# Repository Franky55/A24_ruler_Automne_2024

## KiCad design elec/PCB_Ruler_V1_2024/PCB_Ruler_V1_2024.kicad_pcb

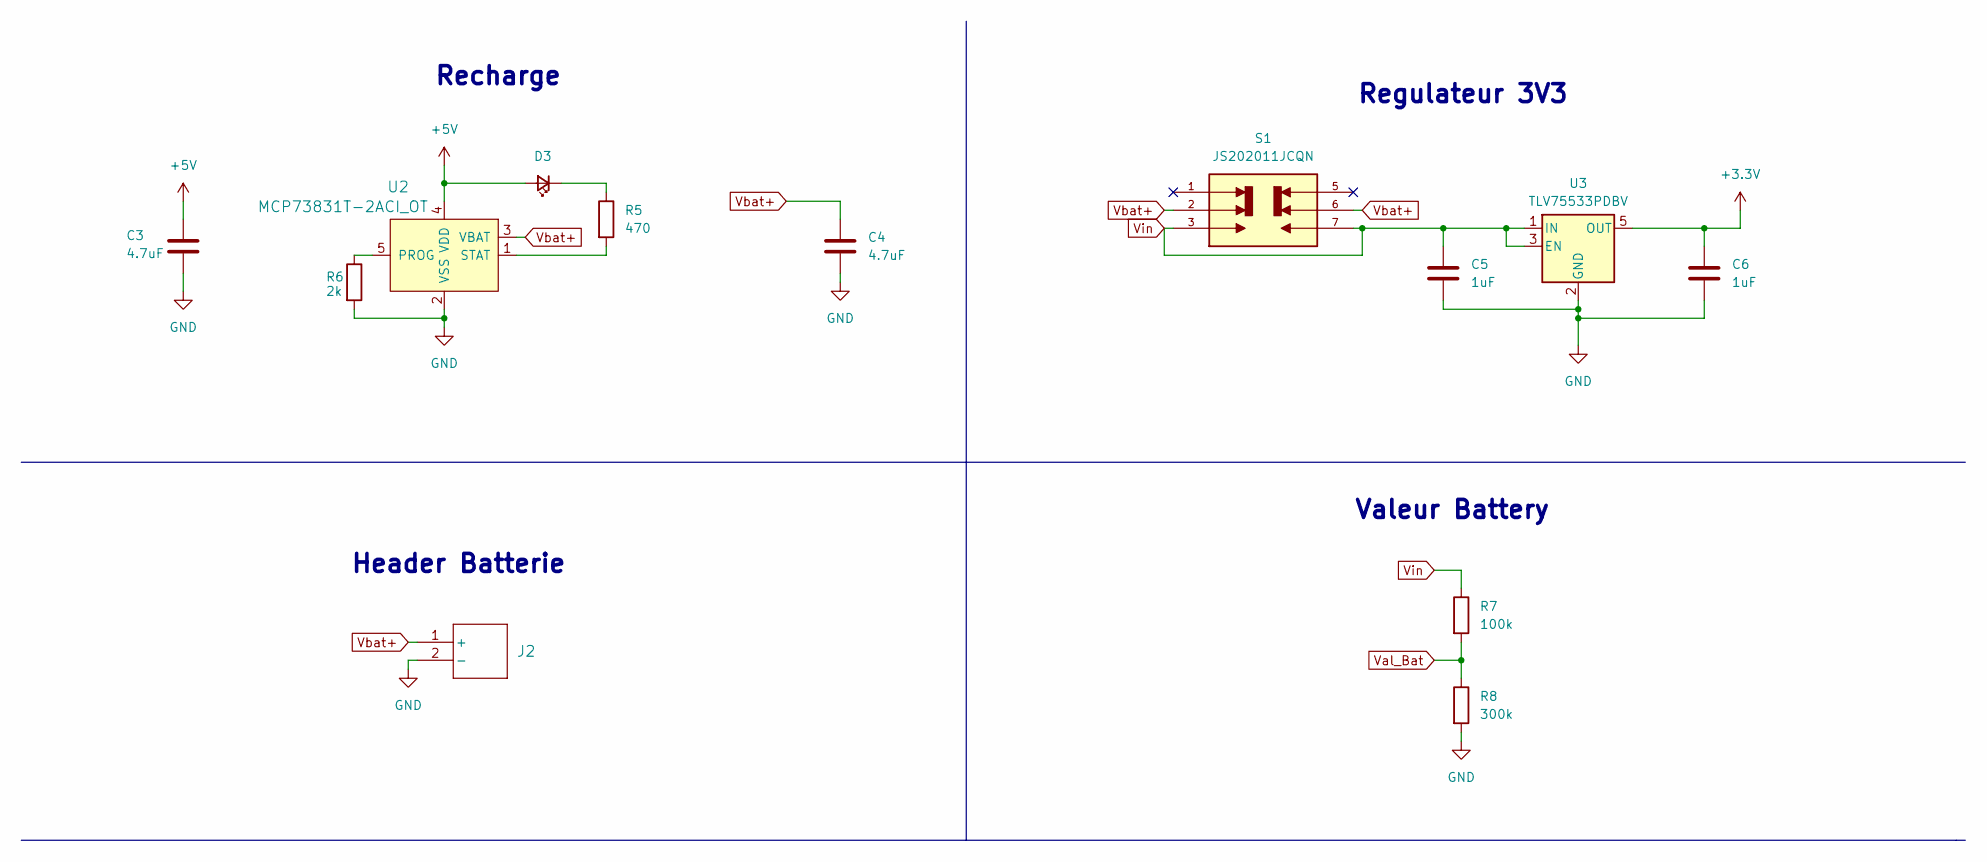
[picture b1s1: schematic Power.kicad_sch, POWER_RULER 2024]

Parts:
C3, C4: 4.7uF; C_0603_1608Metric_Pad1.08x0.95mm_HandSolder
C5, C6: 1uF; C_0603_1608Metric_Pad1.08x0.95mm_HandSolder
D3: LED_Small; LED_0603_1608Metric_Pad1.05x0.95mm_HandSolder
J2: S2B-XH-A-1LFSN; JST_XH_S2B-XH-A-1_1x02_P2.50mm_Horizontal
R5: 470; R_0603_1608Metric_Pad0.98x0.95mm_HandSolder
R6: 2k; R_0603_1608Metric_Pad0.98x0.95mm_HandSolder
R7: 100k; R_0603_1608Metric_Pad0.98x0.95mm_HandSolder
R8: 300k; R_0603_1608Metric_Pad0.98x0.95mm_HandSolder
S1: JS202011JCQN; SW_JS202011JCQN; PARTREV 11 Nov 19
U2: MCP73831T-2ACI_OT; SOT-753; MPN MCP73831T-2ACI/OT; Digi-Key_PN MCP73831T-2ACI/OTCT-ND
U3: TLV75533PDBV; SOT-23-5

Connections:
+5V: C3.1, D3.2 (A), U2.4 (VDD); also elsewhere on the board
AVDD: C6.1, U3.5 (OUT); also elsewhere on the board
GND: C3.2, C4.2, C5.2, C6.2, J2.2 (-), R6.2, R8.2, U2.2 (VSS), U3.2 (GND); also elsewhere on the board
unnamed: D3.1 (K), R5.1
unnamed: R6.1, U2.5 (PROG)
unnamed: R5.2, U2.1 (STAT)
Val_Bat: R7.2, R8.1; also elsewhere on the board
Vbat+: C4.1, J2.1 (+), S1.2, S1.6, U2.3 (VBAT)
Vin: C5.1, R7.1, S1.3, S1.7, U3.1 (IN), U3.3 (EN)

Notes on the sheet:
Valeur Battery
Header Batterie
Regulateur 3V3
Recharge

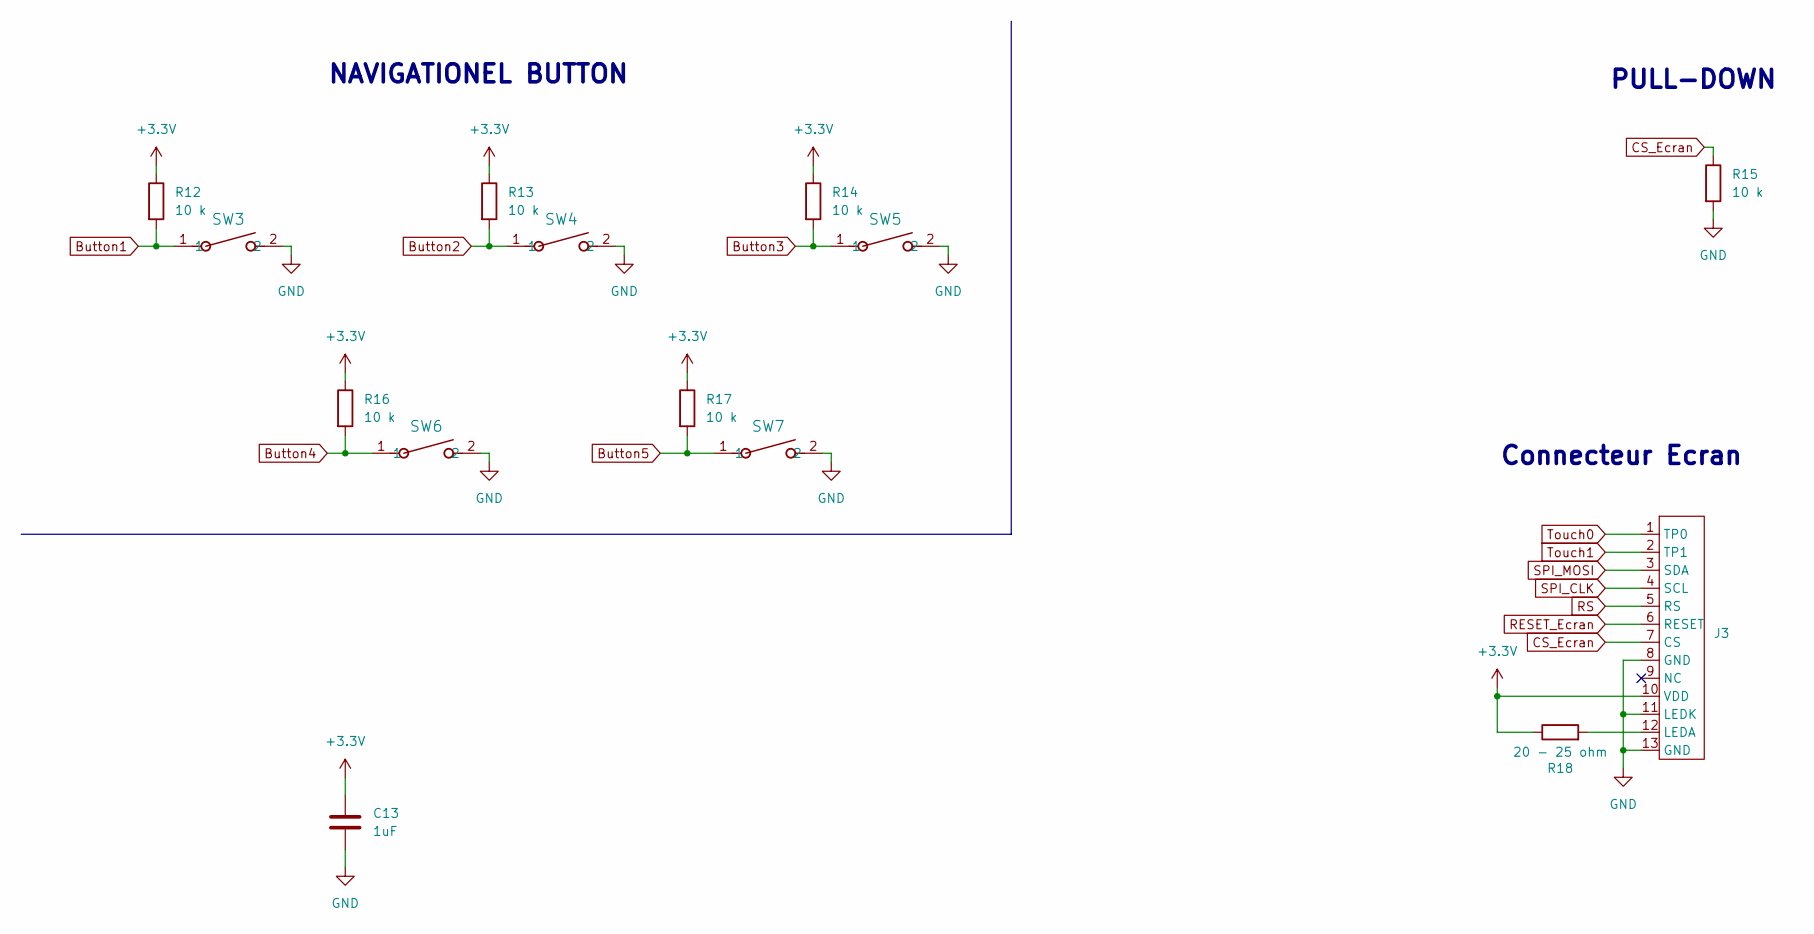
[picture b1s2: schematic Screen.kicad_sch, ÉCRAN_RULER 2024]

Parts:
C13: 1uF; C_0603_1608Metric_Pad1.08x0.95mm_HandSolder
J3: Hirose_FH12-13S-0.5SH_1x13-1MP_P0.50mm_Horizontal
R12, R13, R14, R15, R16, R17: 10 k; R_0603_1608Metric_Pad0.98x0.95mm_HandSolder
R18: 20 - 25 ohm; R_0603_1608Metric_Pad0.98x0.95mm_HandSolder
SW3, SW4, SW5, SW6, SW7: CS1213AGF260; SW_CS1213AGF260_CRS

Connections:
AVDD: C13.1, J3.10 (VDD), R12.1, R13.1, R14.1, R16.1, R17.1, R18.1; also elsewhere on the board
Button1: R12.2, SW3.1; also elsewhere on the board
Button2: R13.2, SW4.1; also elsewhere on the board
Button3: R14.2, SW5.1; also elsewhere on the board
Button4: R16.2, SW6.1; also elsewhere on the board
Button5: R17.2, SW7.1; also elsewhere on the board
CS_Ecran: J3.7 (CS), R15.1; also elsewhere on the board
GND: C13.2, J3.8 (GND), J3.11 (LEDK), J3.13 (GND), R15.2, SW3.2, SW4.2, SW5.2, SW6.2, SW7.2; also elsewhere on the board
unnamed: J3.12 (LEDA), R18.2
RESET_Ecran: J3.6 (RESET); also elsewhere on the board
RS: J3.5 (RS); also elsewhere on the board
SPI_CLK: J3.4 (SCL); also elsewhere on the board
SPI_MOSI: J3.3 (SDA); also elsewhere on the board
Touch0: J3.1 (TP0); also elsewhere on the board
Touch1: J3.2 (TP1); also elsewhere on the board

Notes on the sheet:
NAVIGATIONEL BUTTON
PULL-DOWN
Connecteur Ecran

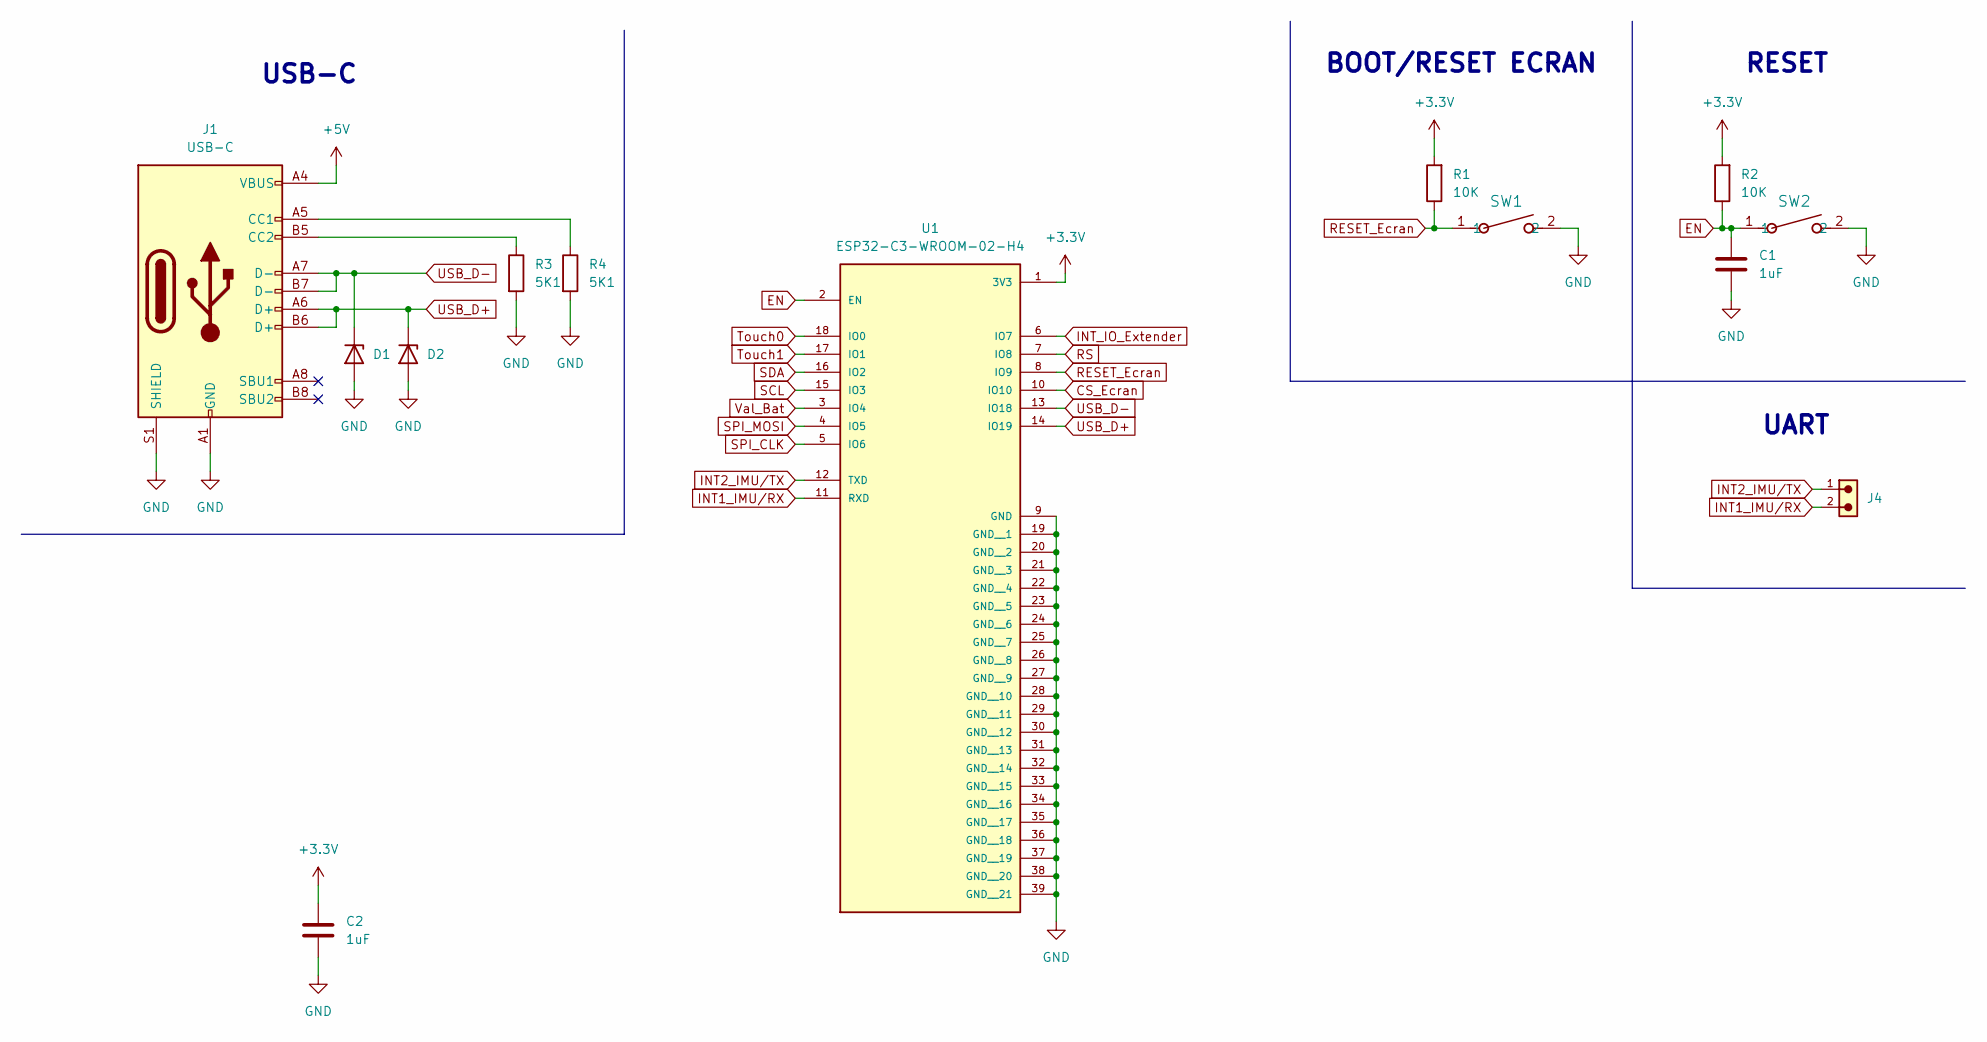
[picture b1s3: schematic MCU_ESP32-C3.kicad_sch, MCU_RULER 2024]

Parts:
C1, C2: 1uF; C_0603_1608Metric_Pad1.08x0.95mm_HandSolder
D1, D2: D_Zener; D_SOD-923
J1: USB-C; USB_C_Receptacle_G-Switch_GT-USB-7010ASV
J4: 61300211121; PART-NUMBER 61300211121
R1, R2: 10K; R_0603_1608Metric_Pad0.98x0.95mm_HandSolder
R3, R4: 5K1; R_0603_1608Metric_Pad0.98x0.95mm_HandSolder
SW1, SW2: CS1213AGF260; SW_CS1213AGF260_CRS
U1: ESP32-C3-WROOM-02-H4; MODULE_ESP32-C3-WROOM-02-H4

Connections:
+5V: J1.A4 (VBUS), J1.A9 (VBUS), J1.B4 (VBUS), J1.B9 (VBUS); also elsewhere on the board
AVDD: C2.1, R1.2, R2.2, U1.1 (3V3); also elsewhere on the board
CS_Ecran: U1.10 (IO10); also elsewhere on the board
EN: C1.1, R2.1, SW2.1, U1.2 (EN)
GND: C1.2, C2.2, D1.2 (A), D2.2 (A), J1.A1 (GND), J1.A12 (GND), J1.B1 (GND), J1.B12 (GND), J1.S1 (SHIELD), R3.2, R4.2, SW1.2, SW2.2, U1.9 (GND), U1.19 (GND__1), U1.20 (GND__2), U1.21 (GND__3), U1.22 (GND__4), U1.23 (GND__5), U1.24 (GND__6), U1.25 (GND__7), U1.26 (GND__8), U1.27 (GND__9), U1.28 (GND__10), U1.29 (GND__11), U1.30 (GND__12), U1.31 (GND__13), U1.32 (GND__14), U1.33 (GND__15), U1.34 (GND__16), U1.35 (GND__17), U1.36 (GND__18), U1.37 (GND__19), U1.38 (GND__20), U1.39 (GND__21); also elsewhere on the board
INT1_IMU/RX: J4.2, U1.11 (RXD); also elsewhere on the board
INT2_IMU/TX: J4.1, U1.12 (TXD); also elsewhere on the board
INT_IO_Extender: U1.6 (IO7); also elsewhere on the board
unnamed: J1.A5 (CC1), R4.1
unnamed: J1.B5 (CC2), R3.1
RESET_Ecran: R1.1, SW1.1, U1.8 (IO9); also elsewhere on the board
RS: U1.7 (IO8); also elsewhere on the board
SCL: U1.15 (IO3); also elsewhere on the board
SDA: U1.16 (IO2); also elsewhere on the board
SPI_CLK: U1.5 (IO6); also elsewhere on the board
SPI_MOSI: U1.4 (IO5); also elsewhere on the board
Touch0: U1.18 (IO0); also elsewhere on the board
Touch1: U1.17 (IO1); also elsewhere on the board
USB_D+: D2.1 (K), J1.A6 (D+), J1.B6 (D+), U1.14 (IO19)
USB_D-: D1.1 (K), J1.A7 (D-), J1.B7 (D-), U1.13 (IO18)
Val_Bat: U1.3 (IO4); also elsewhere on the board

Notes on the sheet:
RESET
UART
USB-C
BOOT/RESET ECRAN

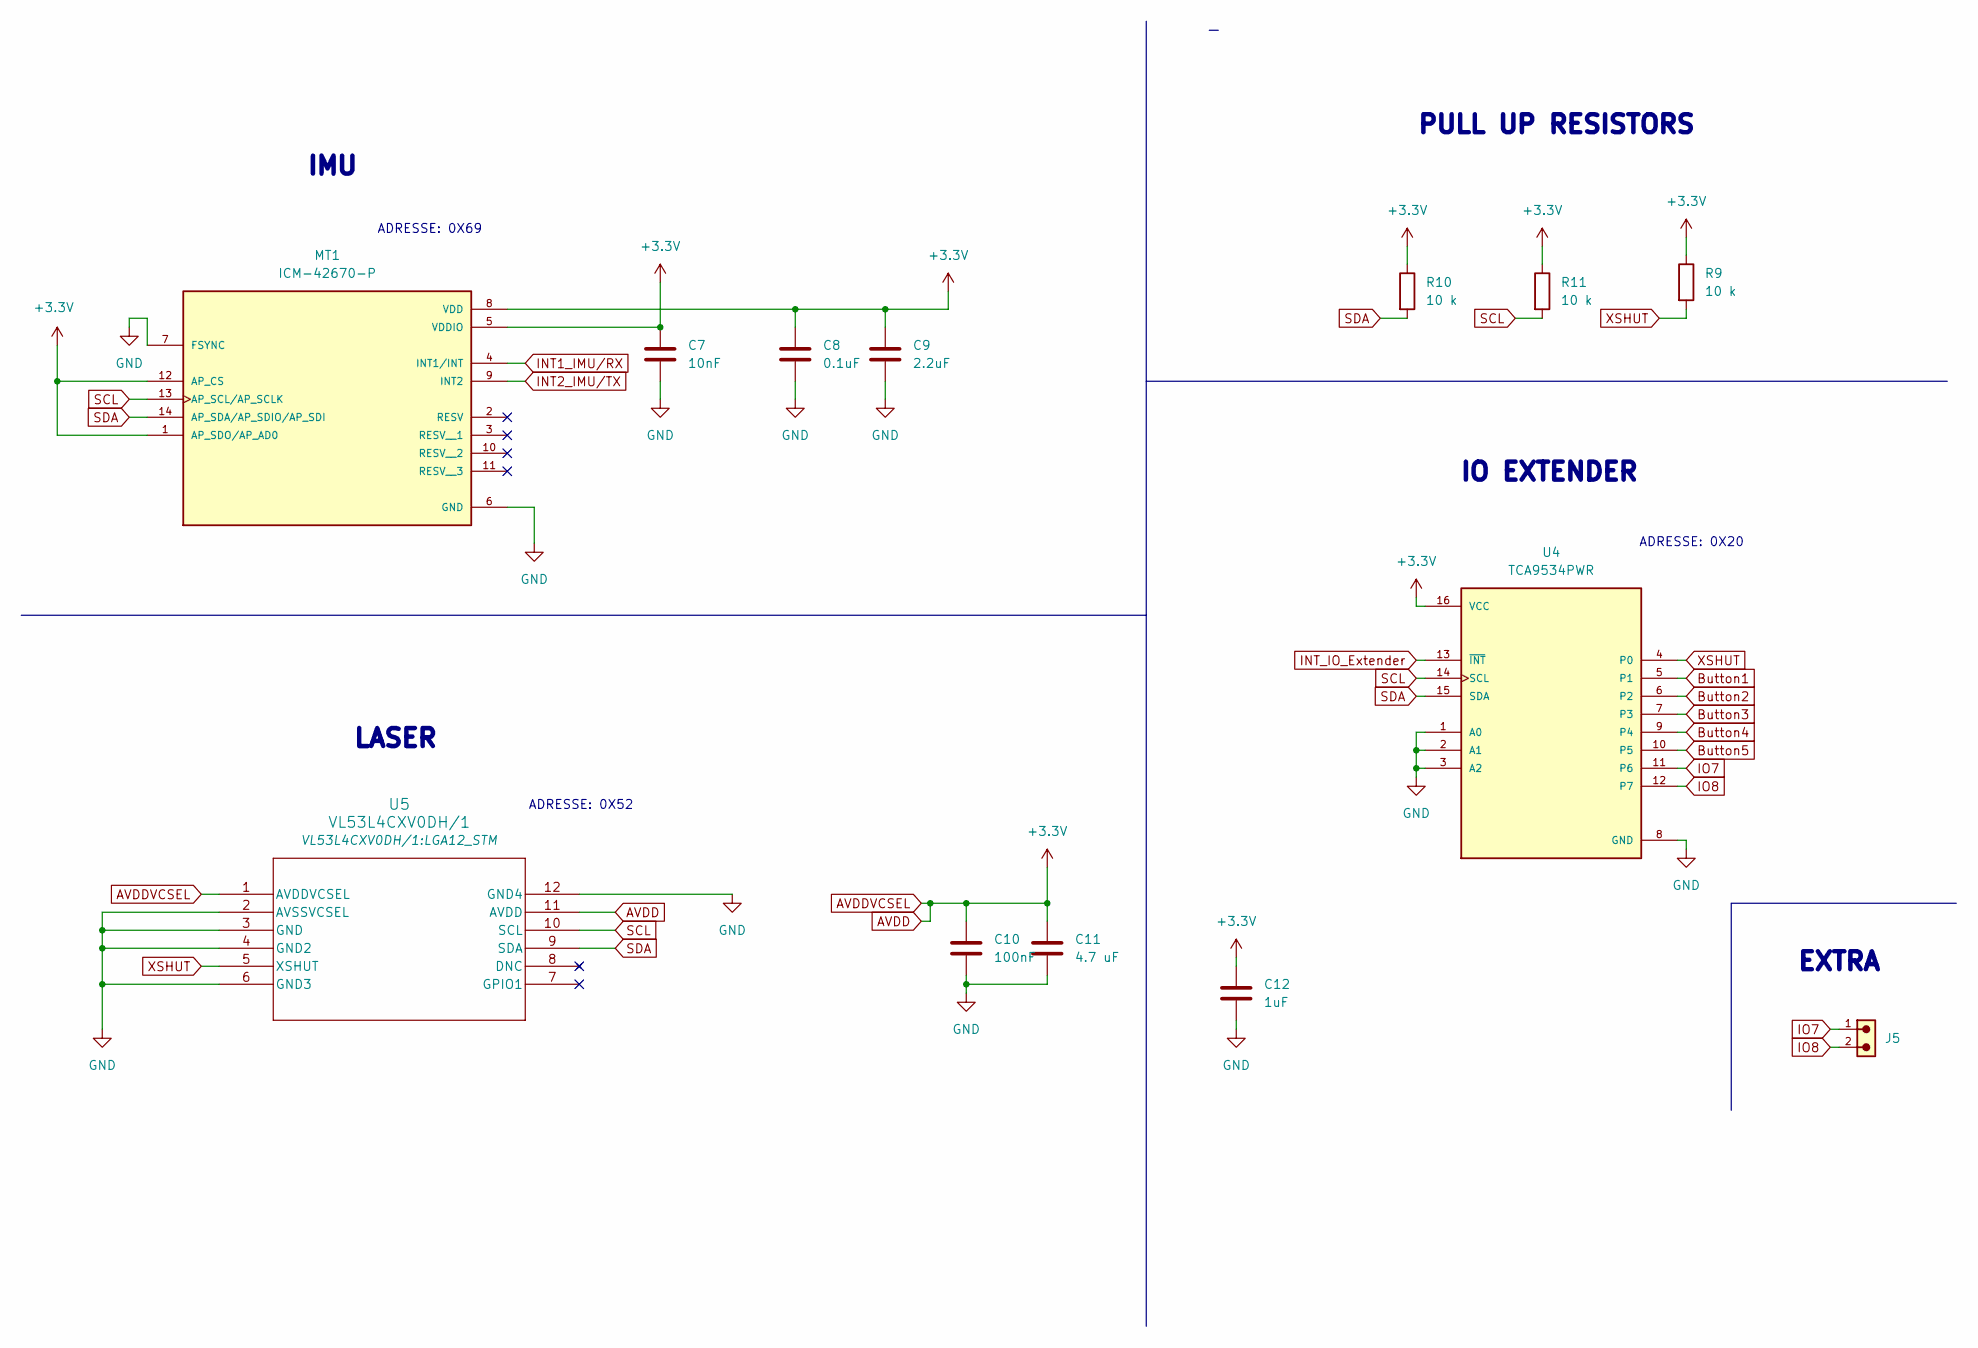
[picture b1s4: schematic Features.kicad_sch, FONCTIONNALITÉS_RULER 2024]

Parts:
C7: 10nF; C_0603_1608Metric_Pad1.08x0.95mm_HandSolder
C8: 0.1uF; C_0603_1608Metric_Pad1.08x0.95mm_HandSolder
C9: 2.2uF; C_0603_1608Metric_Pad1.08x0.95mm_HandSolder
C10: 100nF; C_0603_1608Metric_Pad1.08x0.95mm_HandSolder
C11: 4.7 uF; C_0603_1608Metric_Pad1.08x0.95mm_HandSolder
C12: 1uF; C_0603_1608Metric_Pad1.08x0.95mm_HandSolder
J5: 61300211121; PART-NUMBER 61300211121
MT1: ICM-42670-P; XDCR_ICM-42670-P; PARTREV 1.1
R9, R10, R11: 10 k; R_0603_1608Metric_Pad0.98x0.95mm_HandSolder
U4: TCA9534PWR; SOP65P640X120-16N; PARTREV D
U5: VL53L4CXV0DH/1; LGA12_STM

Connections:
AVDD: C7.1, C8.1, C9.1, C10.1, C11.1, C12.1, MT1.1 (AP_SDO/AP_AD0), MT1.5 (VDDIO), MT1.8 (VDD), MT1.12 (AP_CS), R9.1, R10.1, R11.1, U4.16 (VCC), U5.1 (AVDDVCSEL), U5.11 (AVDD); also elsewhere on the board
Button1: U4.5 (P1); also elsewhere on the board
Button2: U4.6 (P2); also elsewhere on the board
Button3: U4.7 (P3); also elsewhere on the board
Button4: U4.9 (P4); also elsewhere on the board
Button5: U4.10 (P5); also elsewhere on the board
GND: C7.2, C8.2, C9.2, C10.2, C11.2, C12.2, MT1.6 (GND), MT1.7 (FSYNC), U4.1 (A0), U4.2 (A1), U4.3 (A2), U4.8 (GND), U5.2 (AVSSVCSEL), U5.3 (GND), U5.4 (GND2), U5.6 (GND3), U5.12 (GND4); also elsewhere on the board
INT1_IMU/RX: MT1.4 (INT1/INT); also elsewhere on the board
INT2_IMU/TX: MT1.9 (INT2); also elsewhere on the board
INT_IO_Extender: U4.13 (~INT); also elsewhere on the board
IO7: J5.1, U4.11 (P6)
IO8: J5.2, U4.12 (P7)
SCL: MT1.13 (AP_SCL/AP_SCLK), R11.2, U4.14 (SCL), U5.10 (SCL); also elsewhere on the board
SDA: MT1.14 (AP_SDA/AP_SDIO/AP_SDI), R10.2, U4.15 (SDA), U5.9 (SDA); also elsewhere on the board
XSHUT: R9.2, U4.4 (P0), U5.5 (XSHUT)

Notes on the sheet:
IMU
ADRESSE: 0X20
ADRESSE: 0X52
ADRESSE: 0X69
IO EXTENDER
LASER
EXTRA
PULL UP RESISTORS

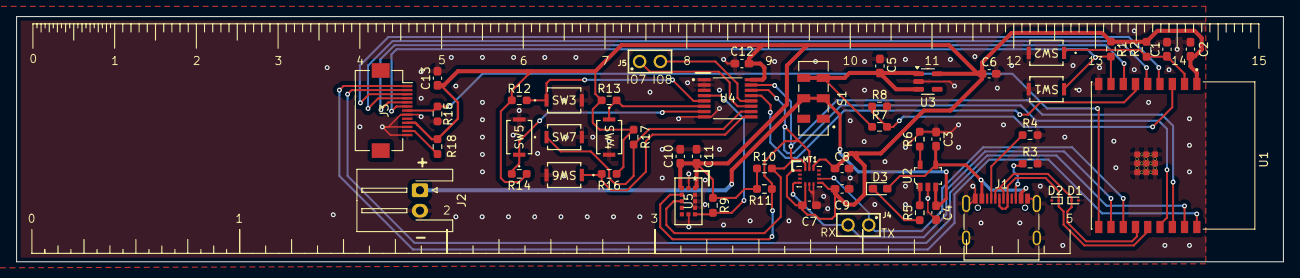
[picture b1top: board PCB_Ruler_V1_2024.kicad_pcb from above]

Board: 2 copper layers, 155.0 x 30.0 mm, 53 parts (0 on the bottom side), 35 nets.

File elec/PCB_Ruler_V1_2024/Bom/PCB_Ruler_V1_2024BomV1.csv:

Reference,Value,Datasheet,Footprint,Qty,DNP
"C1,C2,C5,C6,C12,C13",1uF,~,Capacitor_SMD:C_0603_1608Metric_Pad1.08x0.95mm_HandSolder,6,
"C3,C4",4.7uF,~,Capacitor_SMD:C_0603_1608Metric_Pad1.08x0.95mm_HandSolder,2,
C7,10nF,~,Capacitor_SMD:C_0603_1608Metric_Pad1.08x0.95mm_HandSolder,1,
C8,0.1uF,~,Capacitor_SMD:C_0603_1608Metric_Pad1.08x0.95mm_HandSolder,1,
C9,2.2uF,~,Capacitor_SMD:C_0603_1608Metric_Pad1.08x0.95mm_HandSolder,1,
C10,100nF,~,Capacitor_SMD:C_0603_1608Metric_Pad1.08x0.95mm_HandSolder,1,
C11,4.7 uF,~,Capacitor_SMD:C_0603_1608Metric_Pad1.08x0.95mm_HandSolder,1,
"D1,D2",D_Zener,~,Diode_SMD:D_SOD-923,2,
D3,LED_Small,~,LED_SMD:LED_0603_1608Metric_Pad1.05x0.95mm_HandSolder,1,
J1,USB-C,https://www.usb.org/sites/default/files/documents/usb_type-c.zip,Connector_USB:USB_C_Receptacle_G-Switch_GT-USB-7010ASV,1,
J2,S2B-XH-A-1LFSN,S2B-XH-A-1LFSN,Connector_JST:JST_XH_S2B-XH-A-1_1x02_P2.50mm_Horizontal,1,
J3,~,,Connector_FFC-FPC:Hirose_FH12-13S-0.5SH_1x13-1MP_P0.50mm_Horizontal,1,
MT1,ICM-42670-P,,IMU:XDCR_ICM-42670-P,1,
"R1,R2",10K,~,Resistor_SMD:R_0603_1608Metric_Pad0.98x0.95mm_HandSolder,2,
"R3,R4",5K1,~,Resistor_SMD:R_0603_1608Metric_Pad0.98x0.95mm_HandSolder,2,
R5,470,~,Resistor_SMD:R_0603_1608Metric_Pad0.98x0.95mm_HandSolder,1,
R6,2k,~,Resistor_SMD:R_0603_1608Metric_Pad0.98x0.95mm_HandSolder,1,
R7,100k,~,Resistor_SMD:R_0603_1608Metric_Pad0.98x0.95mm_HandSolder,1,
R8,300k,~,Resistor_SMD:R_0603_1608Metric_Pad0.98x0.95mm_HandSolder,1,
"R9,R10,R11,R12,R13,R14,R15,R16,R17",10 k,~,Resistor_SMD:R_0603_1608Metric_Pad0.98x0.95mm_HandSolder,9,
R18,20 - 25 ohm,~,Resistor_SMD:R_0603_1608Metric_Pad0.98x0.95mm_HandSolder,1,
S1,JS202011JCQN,,JS202011JCQN:SW_JS202011JCQN,1,
"SW1,SW2,SW3,SW4,SW5,SW6,SW7",CS1213AGF260,CS1213AGF260,CS1213AGF260:SW_CS1213AGF260_CRS,7,
U1,ESP32-C3-WROOM-02-H4,,ESP32_C3_WROOM_02_H4:MODULE_ESP32-C3-WROOM-02-H4,1,
U2,MCP73831T-2ACI_OT,http://ww1.microchip.com/downloads/en/DeviceDoc/20001984g.pdf,digikey-footprints:SOT-753,1,
U3,TLV75533PDBV,http://www.ti.com/lit/ds/symlink/tlv755p.pdf,Package_TO_SOT_SMD:SOT-23-5,1,
U4,TCA9534PWR,,TCA9534PWR:SOP65P640X120-16N,1,
U5,VL53L4CXV0DH/1,VL53L4CXV0DH/1,VL53L4CXV0DH/1:LGA12_STM,1,

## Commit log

2024-10-14 Made kicad first push
2024-11-02 first actual push
2024-11-03 battery charger
2024-11-03 this is for my strong girl
2024-11-03 Laser
2024-11-04 regulator 3V3
2024-11-05 Almost finished schematic...
2024-11-05 Forgot to close the file
2024-11-05 protection and Buttons
2024-11-05 idk, new change
2024-11-07 started pcb
2024-11-07 pull down
2024-11-08 Hi handsome :)
2024-11-12 modified pcb order
2024-11-15 Je les ai mis ensemble mais pour les places en tant que tel pas sur , pas sur
2024-11-16 yeah
2024-11-16 modifs :D
2024-11-17 allo
2024-11-18 started the pcb
2024-11-18 meeting miriam
2024-11-22 Added to schematic what was missing
2024-11-22 hi sexy ;)
2024-11-22 PCB no errors
2024-11-23 last push before order
2024-11-23 changed name
2024-12-23 Truss
2024-12-24 coding simulator
2024-12-24 web site, buttons, IMU
2024-12-26 we have web
2024-12-27 Hi good-looking ;)
2024-12-28 functionnal version
2024-12-28 coucou
2024-12-28 coucou v2
2024-12-28 Dernier push avant remise
2024-12-28 yes, always another push
